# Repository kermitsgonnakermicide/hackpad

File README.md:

# The LTTPad 
This Hackpad was built as a fun little intro to the whole Highway thing - It contains:<br>
5x Keys<Br>
1x Encoder and<br>
1x 128x32 OLED Display<br>
This is powered by a Xiao RP2040 and the firmware will be KMK<br>
  
.png)<br>
.png)<br>
.png)<br>

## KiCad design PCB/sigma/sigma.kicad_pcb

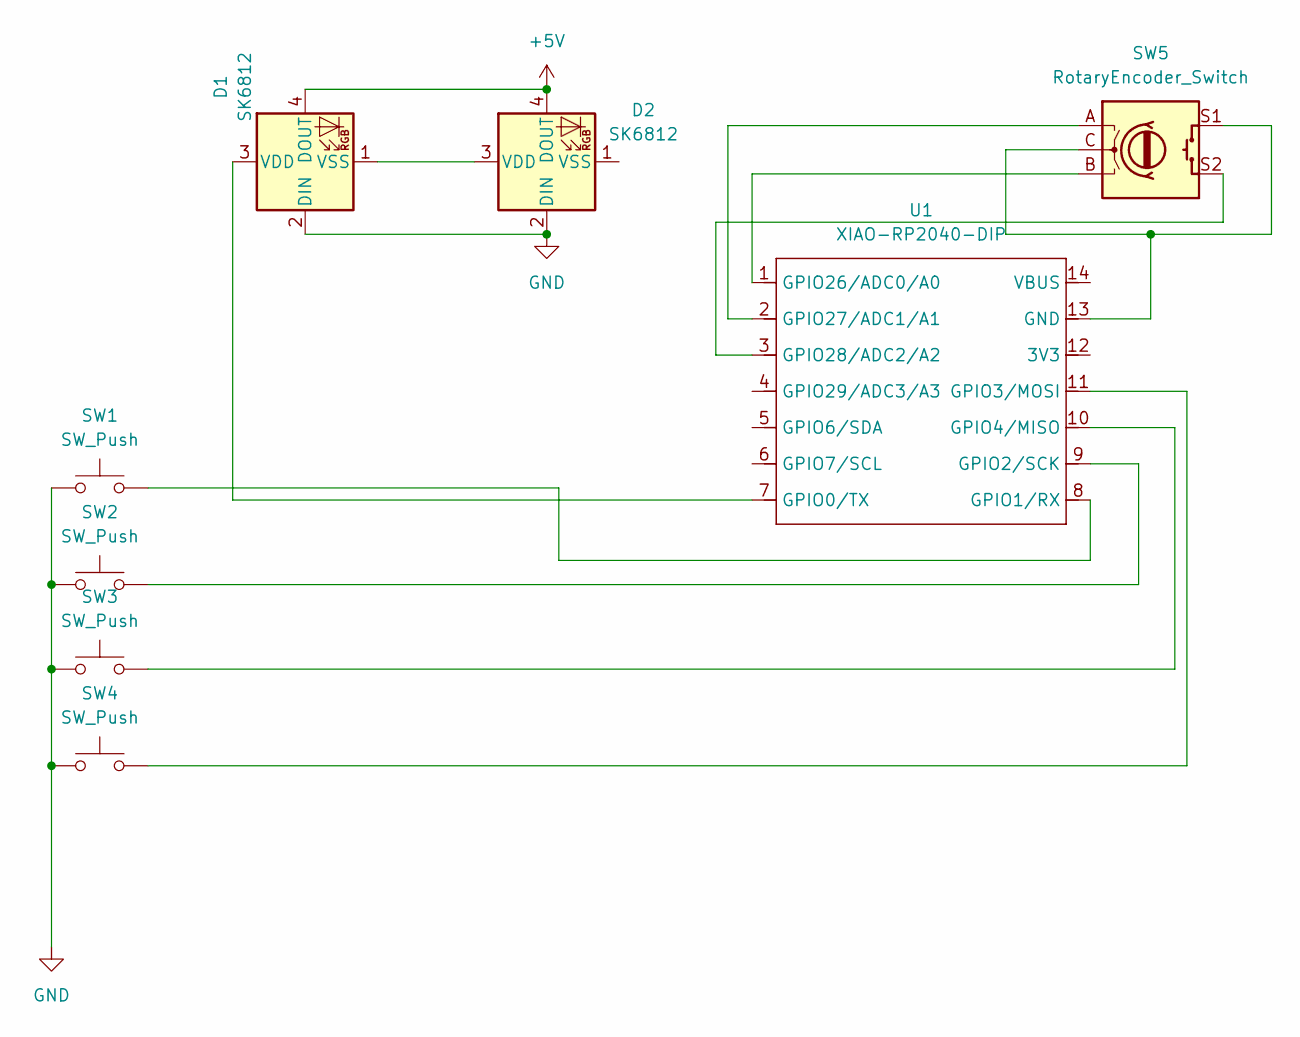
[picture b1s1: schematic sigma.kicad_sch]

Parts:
D1, D2: SK6812; LED_SK6812_PLCC4_5.0x5.0mm_P3.2mm
SW1, SW2, SW3, SW4: SW_Push; SW_Cherry_MX_1.00u_PCB
SW5: RotaryEncoder_Switch; RotaryEncoder_Alps_EC11E-Switch_Vertical_H20mm_CircularMoun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
U1: XIAO-RP2040-DIP

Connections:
+5V: D1.4 (DOUT), D2.4 (DOUT)
GND: D1.2 (DIN), D2.2 (DIN), SW1.1, SW2.1, SW3.1, SW4.1
unnamed: D1.3 (VDD), U1.7 (GPIO0/TX)
unnamed: D1.1 (VSS), D2.3 (VDD)
unnamed: SW5.C, SW5.S1, U1.13 (GND)
unnamed: SW1.2, U1.8 (GPIO1/RX)
unnamed: SW2.2, U1.9 (GPIO2/SCK)
unnamed: SW4.2, U1.11 (GPIO3/MOSI)
unnamed: SW3.2, U1.10 (GPIO4/MISO)
unnamed: SW5.B, U1.1 (GPIO26/ADC0/A0)
unnamed: SW5.A, U1.2 (GPIO27/ADC1/A1)
unnamed: SW5.S2, U1.3 (GPIO28/ADC2/A2)

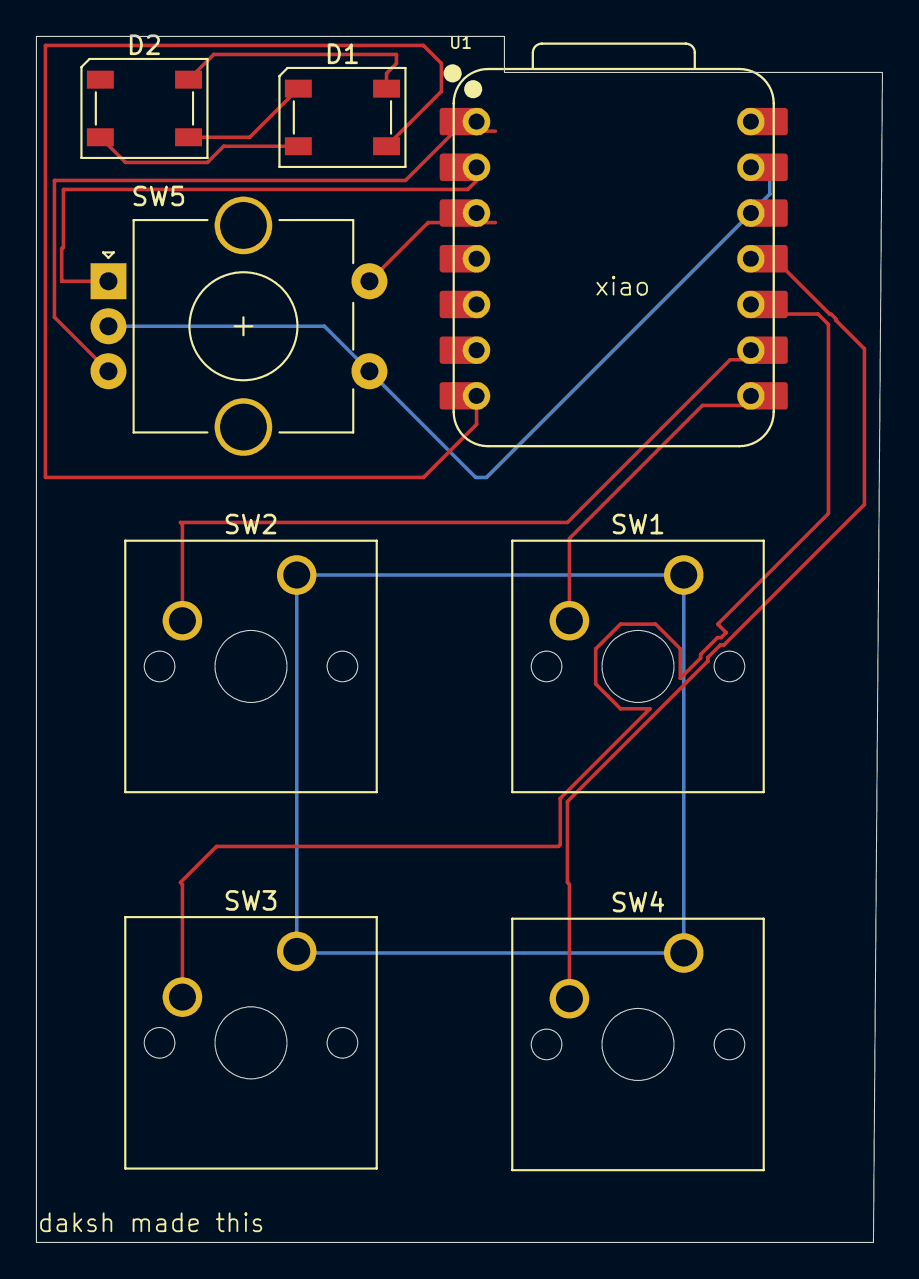
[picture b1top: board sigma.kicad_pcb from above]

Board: 2 copper layers, 47.0 x 67.0 mm, 8 parts (0 on the bottom side), 12 nets.

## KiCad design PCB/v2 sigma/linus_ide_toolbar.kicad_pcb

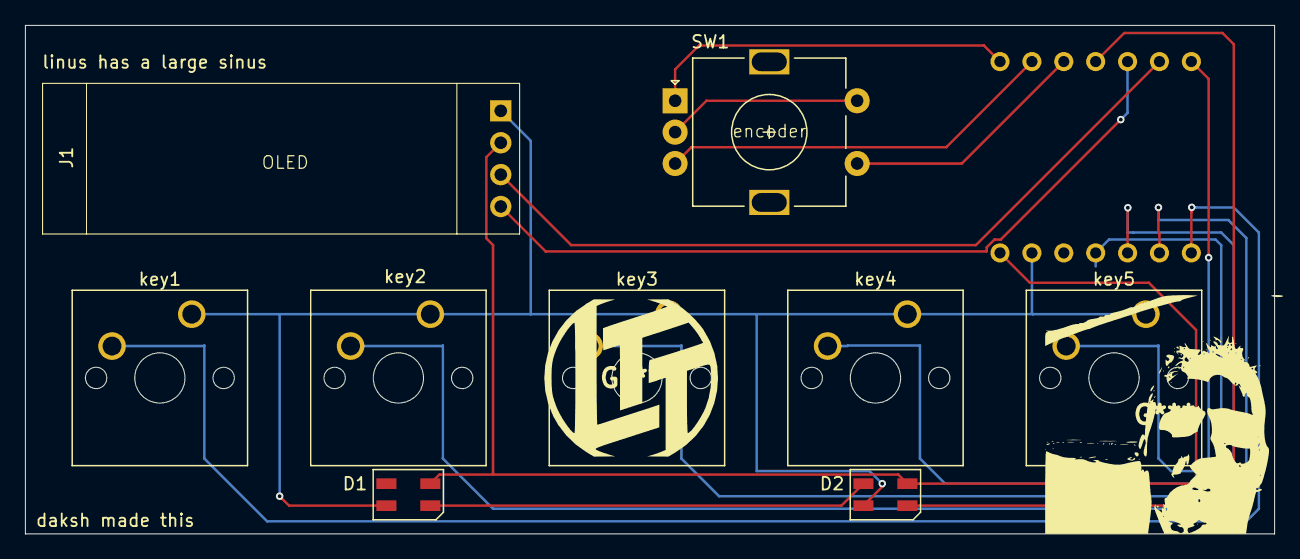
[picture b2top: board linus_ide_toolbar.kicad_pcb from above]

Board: 2 copper layers, 99.5 x 40.5 mm, 10 parts (1 on the bottom side), 15 nets.

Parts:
Continue1: SW_Push; SW_Cherry_MX_1.00u_PCB
D1, D2: SK6812MINI; LED_SK6812MINI_PLCC4_3.5x3.5mm_P1.75mm
J1: Conn_01x04_Pin; SSD1306-0.91-OLED-4pin-128x32
SW1: RotaryEncoder_Switch; RotaryEncoder_Alps_EC11E-Switch_Vertical_H20mm
Stop1: SW_Push; SW_Cherry_MX_1.00u_PCB
U1: XIAO-RP2040-DIP
key1, key4, key5: SW_Push; SW_Cherry_MX_1.00u_PCB

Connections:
+5V: D1.4 (VDD), D2.4 (VDD), J1.2, U1.14 (VBUS)
GND: Continue1.1, D1.2 (VSS), D2.2 (VSS), J1.1, Stop1.1, U1.13 (GND), key1.1, key4.1, key5.1
unnamed: D1.3 (DIN), D2.1 (DOUT)
unnamed: D2.3 (DIN), U1.4 (GPIO29/ADC3/A3)
unnamed: J1.3, U1.6 (GPIO7/SCL)
unnamed: J1.4, U1.5 (GPIO6/SDA)
unnamed: SW1.C, SW1.S2
unnamed: U1.7 (GPIO0/TX), key5.2
unnamed: U1.8 (GPIO1/RX), key1.2
unnamed: Stop1.2, U1.9 (GPIO2/SCK)
unnamed: U1.11 (GPIO3/MOSI), key4.2
unnamed: Continue1.2, U1.10 (GPIO4/MISO)
unnamed: SW1.A, U1.1 (GPIO26/ADC0/A0)
unnamed: SW1.B, U1.2 (GPIO27/ADC1/A1)
unnamed: SW1.S1, U1.3 (GPIO28/ADC2/A2)

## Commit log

2025-05-27 AAAA
2025-05-28 final
2025-06-05 almost
2025-06-05 images
